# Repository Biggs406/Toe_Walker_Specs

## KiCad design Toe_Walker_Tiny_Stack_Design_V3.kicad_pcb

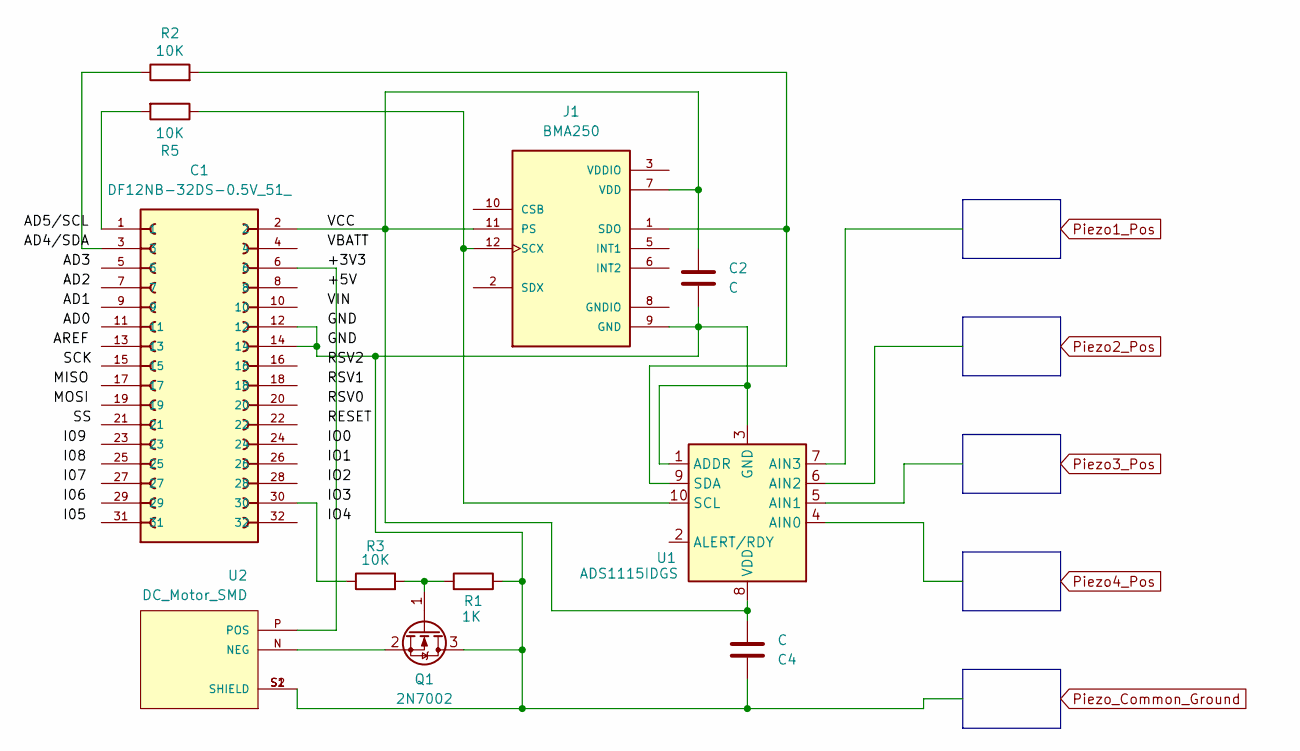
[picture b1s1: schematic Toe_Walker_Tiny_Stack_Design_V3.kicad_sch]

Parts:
C1: DF12NB-32DS-0.5V_51_; HRS_DF12NB-32DS-0.5V_51_
C2, C4: C; C_0201_0603Metric_Pad0.64x0.40mm_HandSolder
J1: BMA250; LGA12S50P4X4_200X200X100
Q1: 2N7002; SOT-23
R1: 1K; R_0805_2012Metric_Pad1.20x1.40mm_HandSolder
R2, R3, R5: 10K; R_0805_2012Metric_Pad1.20x1.40mm_HandSolder
U1: ADS1115IDGS; TSSOP-10_3x3mm_P0.5mm
U2: DC_Motor_SMD; JINLONG_Z6DCBB0056091; PARTREV 2011.11.15

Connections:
/+3V3: C1.6, U2.P (POS)
/VCC: C1.2, C2.1, C4.2, J1.7 (VDD), J1.11 (PS), U1.8 (VDD)
unnamed: C1.1, R5.2
unnamed: C1.3, R2.1
unnamed: C1.30, R3.1
unnamed: C1.12, C1.14, C2.2, C4.1, J1.9 (GND), Q1.3 (D), R1.1, U1.1 (ADDR), U1.3 (GND), U2.S1 (SHIELD), U2.S2 (SHIELD)
unnamed: J1.12 (SCX), R5.1, U1.10 (SCL)
unnamed: J1.1 (SDO), R2.2, U1.9 (SDA)
unnamed: Q1.1 (G), R1.2, R3.2
unnamed: Q1.2 (S), U2.N (NEG)

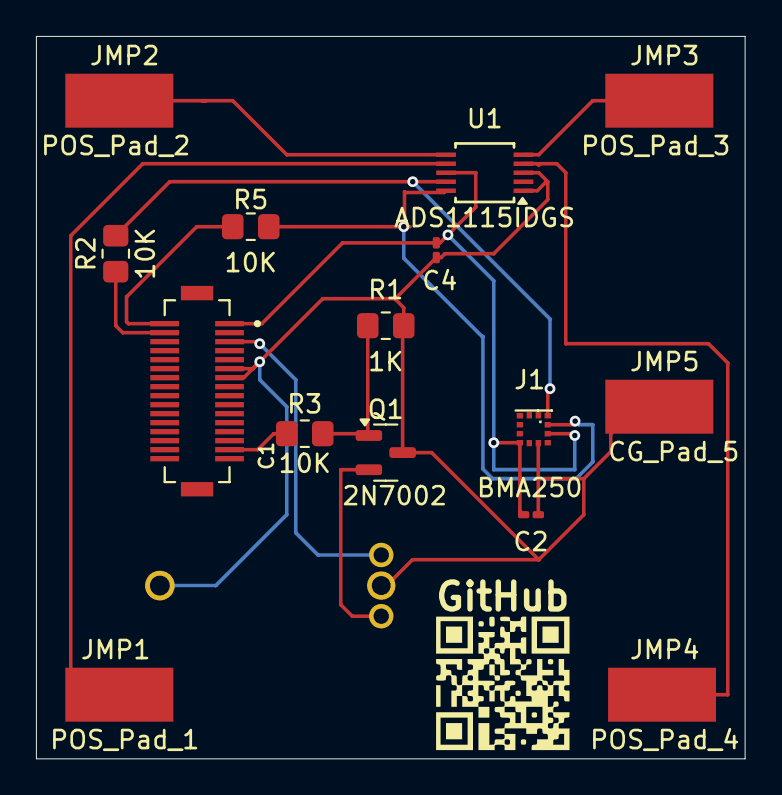
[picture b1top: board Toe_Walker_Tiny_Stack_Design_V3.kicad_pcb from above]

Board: 2 copper layers, 39.4 x 40.1 mm, 17 parts (1 on the bottom side), 10 nets.

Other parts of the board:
GitHub: LOGO
JMP1: POS_Pad_1; SolderJumper-2_P1.3mm_Bridged_RoundedPad1.0x1.5mm
JMP2: POS_Pad_2; SolderJumper-2_P1.3mm_Bridged_RoundedPad1.0x1.5mm
JMP3: POS_Pad_3; SolderJumper-2_P1.3mm_Bridged_RoundedPad1.0x1.5mm
JMP4: POS_Pad_4; SolderJumper-2_P1.3mm_Bridged_RoundedPad1.0x1.5mm
JMP5: CG_Pad_5; SolderJumper-2_P1.3mm_Bridged_RoundedPad1.0x1.5mm

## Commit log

2024-08-15 Create KiCad Files
2024-08-15 Create blank
2024-12-03 Add files via upload
    Arduino Libraries
2024-12-03 Create Arduino_Libraries
2024-12-03 Create empty
